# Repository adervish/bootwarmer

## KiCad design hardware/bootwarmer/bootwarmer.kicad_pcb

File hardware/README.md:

# Bootwarmer controller board (rev C, integrated)

One board per boot. Each board carries an ESP32-C6 module, one 18650 cell, a
USB-C port for charging and flashing, one heater output, one thermistor input,
and an IMU. JLCPCB places every part except the through-hole battery holder.

Status: **unbuilt first article.** The design passes KiCad's electrical and
design-rule checks and the netlist is verified against the design file, but no
board has been made or powered. Read "Before you order" below.

## What is on the board

| Block | Parts | Notes |
|---|---|---|
| MCU | U1 (ESP32-C6-MINI-1-N4) | Bluetooth LE; built-in antenna overhangs the end of the cell |
| Battery | MPD BH-18650-PC holder on the back | The only hand-soldered part: two through-hole joints |
| Reverse-polarity protection | Q1, Q2 (AO3401A), R6 | A cell inserted backwards is blocked |
| Cell protection | U3 (DW01A), Q3, Q4 (AO3400A) | Over-discharge, over-charge, short circuit; trips at roughly 2.5-3 A |
| USB-C and charger | J1, U5, U2 (TP4056), about 0.6 A | Red = charging, green = done. Same port flashes firmware |
| 3.3 V supply | U4 (ME6211), SW1 | The slide switch enables the regulator |
| Heater output | J2, Q5 (AO3400A), R23, R24, C3 | Low-side switch, 100 Hz PWM, off by default |
| Thermistor input | J4, R21 (5.1k), C12 | 10k NTC (B3950) between the two pins |
| IMU | U6 (LSM6DS3TR-C), I2C address 0x6A | |
| Status | LED3, SW2 (BOOT) | |
| Test pads | TP1 GND, TP2 3V3, TP3 VSYS | |

Board: 107 x 27.4 mm, 2 layers, about 24 mm thick with the holder.

## Pin map

| GPIO | Net | Use |
|---|---|---|
| IO14 | HTR1 | Heater MOSFET gate, high = heat |
| IO1 | NTC1 | Thermistor divider (ADC) |
| IO0 | VBAT_SENSE | Battery voltage / 2 (ADC) |
| IO6 | VBUS_SENSE | USB present, VBUS / 2 (ADC) |
| IO7 / IO18 | SDA / SCL | IMU |
| IO19 | IMU_INT | IMU interrupt 1 |
| IO8 | LED_STAT | Status LED, low = on (strapping pin, pulled high) |
| IO9 | BOOT | Boot button to ground (strapping pin, pulled high) |
| IO12 / IO13 | USB_DN / USB_DP | USB-C data |

## Ordering from JLCPCB

Files are in `fab/`:

1. Upload `bootwarmer-gerbers.zip`. 2 layers, 1.6 mm, LeadFree HASL.
2. Turn on PCB Assembly, **Standard** type, top side. The ESP32 module and the
   IMU are not available with Economic assembly.
3. Upload `bootwarmer-bom.csv` and `bootwarmer-cpl.csv`. 54 parts are placed.
4. Confirm stock for every line. The module (C5736265) has been out of stock at
   times; the -H4 and -N8 variants of ESP32-C6-MINI-1 use the same footprint.
5. Set Confirm Parts Placement to Yes and check the placement preview.
   JLCPCB's rotation convention differs from KiCad's for some packages. Look at
   U1, U2, U3, U4, U5, U6, the SOT-23 transistors, the LEDs, J1 and SW1.
6. J2 and J4 use a JST-PH-compatible connector (CJT A2001WR-S-2P) on a footprint
   drawn for the genuine JST part. Check that they sit on their pads.

Parts you add yourself:

- **BT1**: MPD BH-18650-PC holder, soldered on the back. `+` end is at the USB end.
- Heater and thermistor leads need JST PH 2-pin plugs.

## Before you order

- **Heater resistance.** The heater runs from 3.0-4.2 V. A pad of about
  2.5-3.5 ohms gives roughly 4-6 W. Pads sized for 5 V will make about half
  their rated heat. Keep heater current under 2 A (connector rating).
- **Run time.** A 3000 mAh cell holds about 11 Wh: roughly 2 hours at a
  continuous 5 W, longer when the PID loop is cycling, less in the cold.
- **Thermal cutoff.** Firmware cuts the heater at 130 F and on any sensor
  fault, and a watchdog resets a hung controller. Nothing independent of
  firmware limits pad temperature. A 60 C thermal fuse in series with the pad,
  taped to it, is strongly recommended.
- **Unprotected flat-top 18650 cells.** Protected cells are usually too long
  for this holder. The spring contacts can bounce under hard impacts.
- **Thermistor accuracy** assumes a 3.3 V rail. Below about 3.4 V of battery
  the rail sags and readings drift; firmware stops heating at 3.3 V.
- The heater current loop is laid out by hand with wide copper; the rest is
  autorouted. Open `bootwarmer/bootwarmer.kicad_pcb` in KiCad and look it over.

## Bring-up

1. Before fitting the holder, check for shorts with a meter: VSYS to GND and
   3V3 to GND.
2. Solder the holder. Insert a cell. TP3 (VSYS) may read 0 V until the charger
   wakes the protection chip; plugging in USB once does that.
3. Switch ON. TP2 should read 3.3 V and the status LED should blink.
4. Plug in USB-C. The red LED lights while charging. Heating is disabled
   whenever USB is plugged in.
5. Flash `src/esp32c6/bootwarmer` (board: ESP32C6 Dev Module, USB CDC On Boot
   enabled). If the port does not appear, hold BOOT while switching ON.
6. Plug in a thermistor and heater, unplug USB, and connect with the app.
   A new board comes up as left; the app's control packet can reassign it.

## Regenerating

Everything is generated from `scripts/design.py`. Edit that file, then run
`./build.sh`. It rebuilds the schematic, places and autoroutes the board,
pours and stitches the ground planes, runs ERC and DRC, verifies both netlists
against the design file, and rewrites `fab/`.

Requirements: KiCad 10, Freerouting 2.5 jar at
`~/.local/share/freerouting/freerouting.jar`, and Java 25 or newer
(`brew install openjdk`).

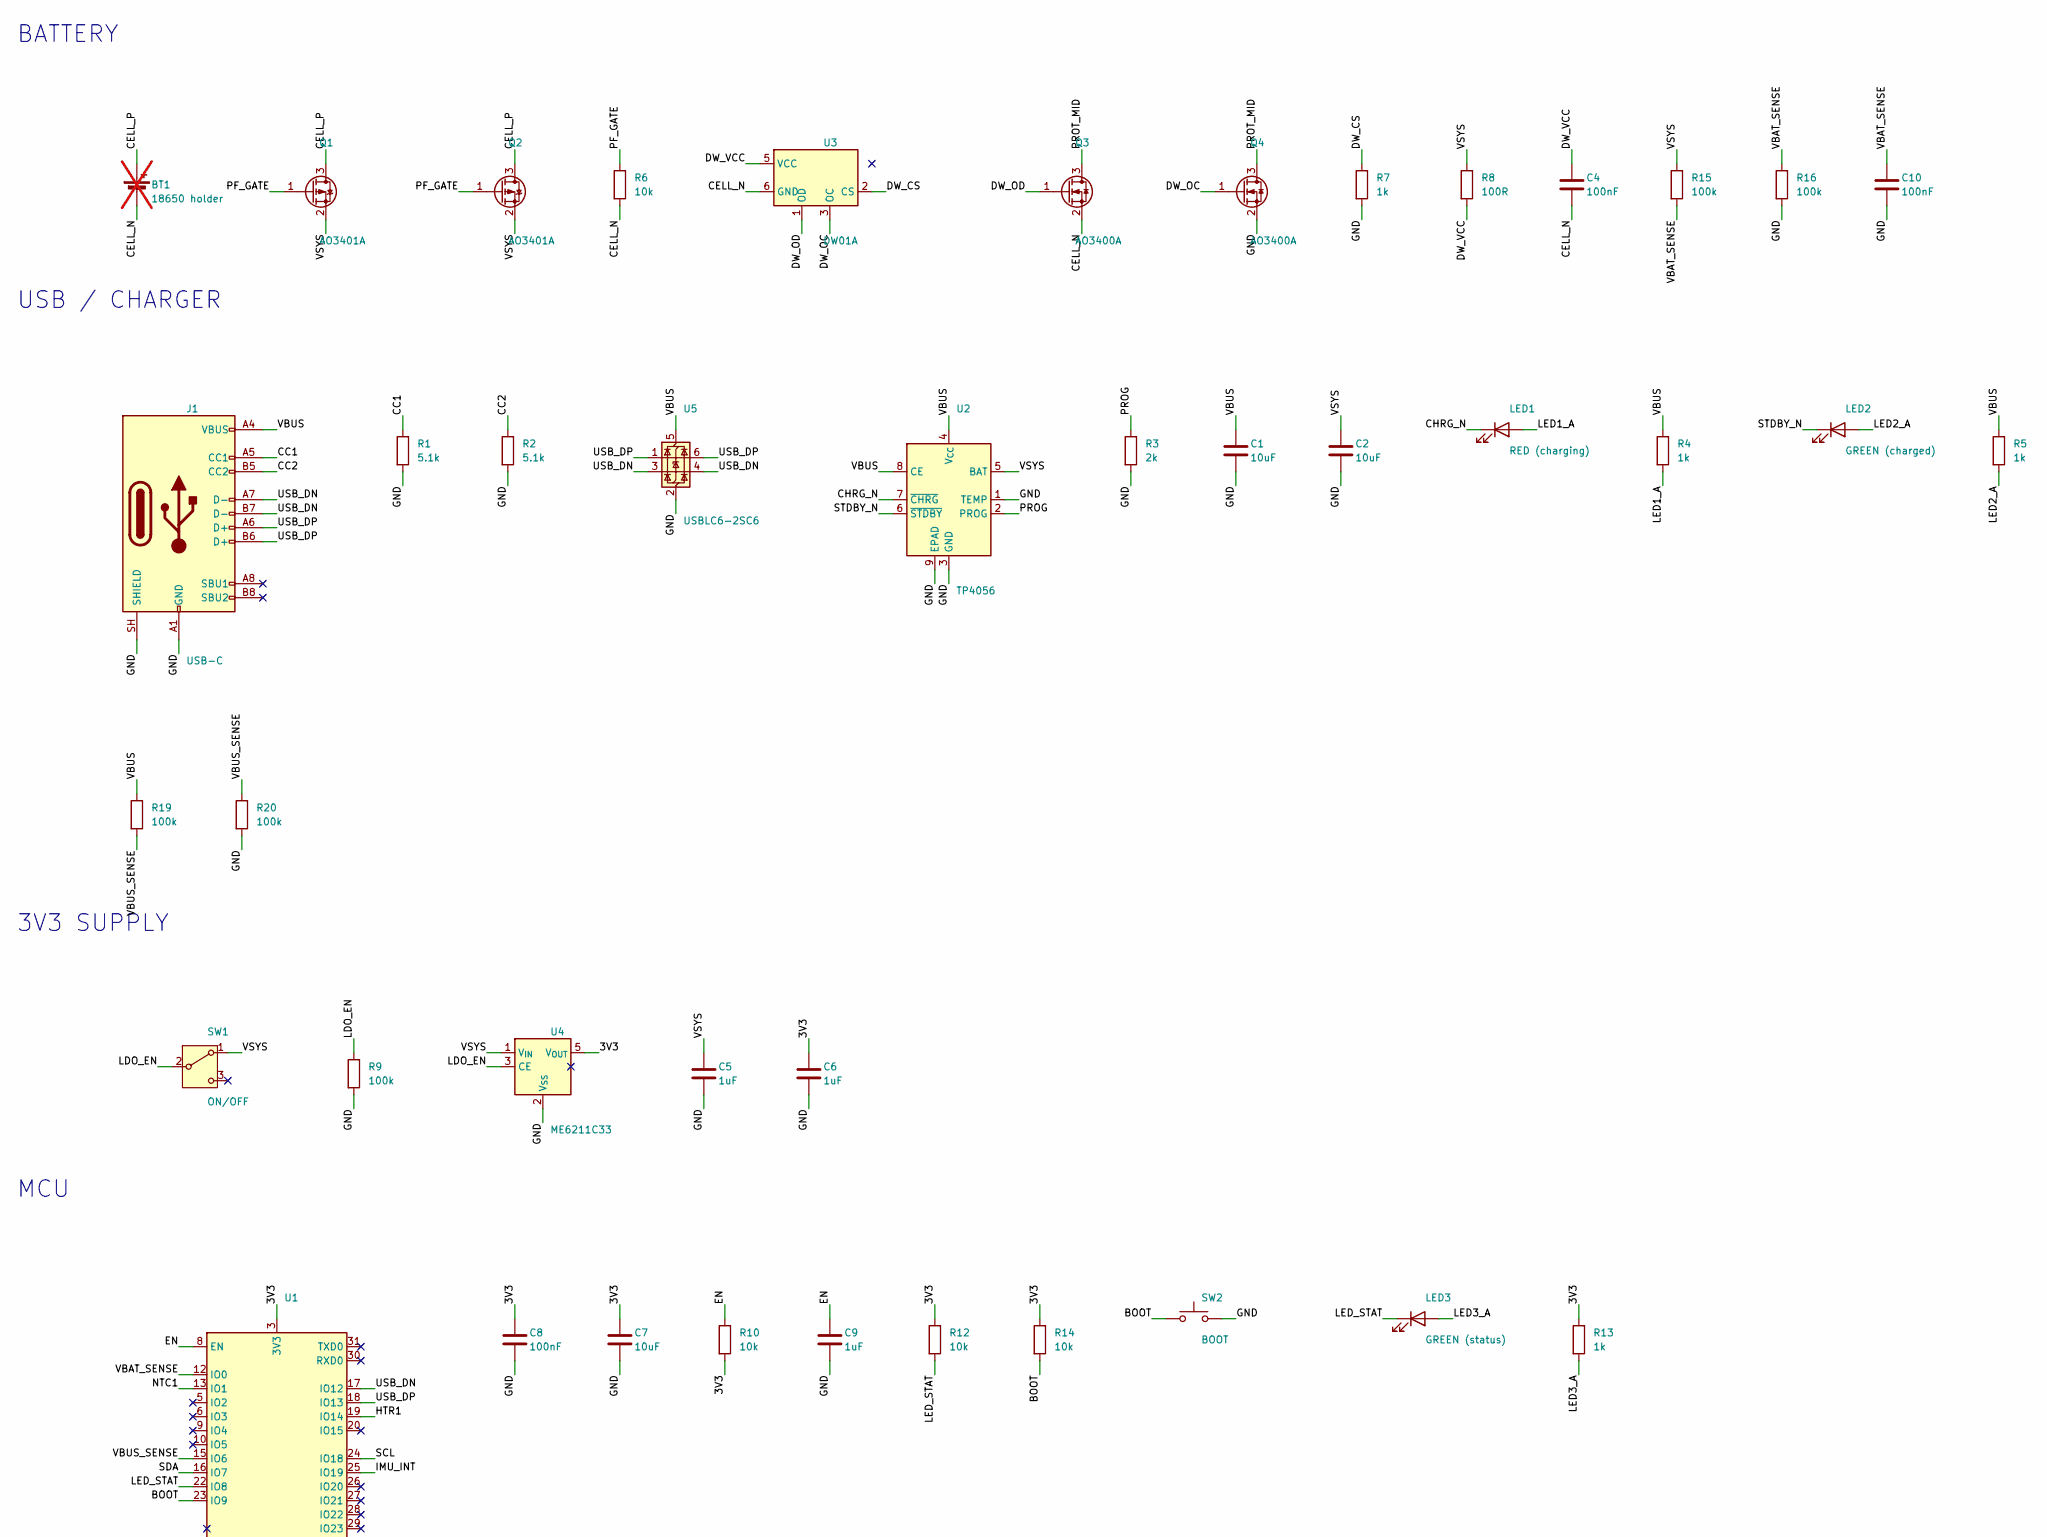
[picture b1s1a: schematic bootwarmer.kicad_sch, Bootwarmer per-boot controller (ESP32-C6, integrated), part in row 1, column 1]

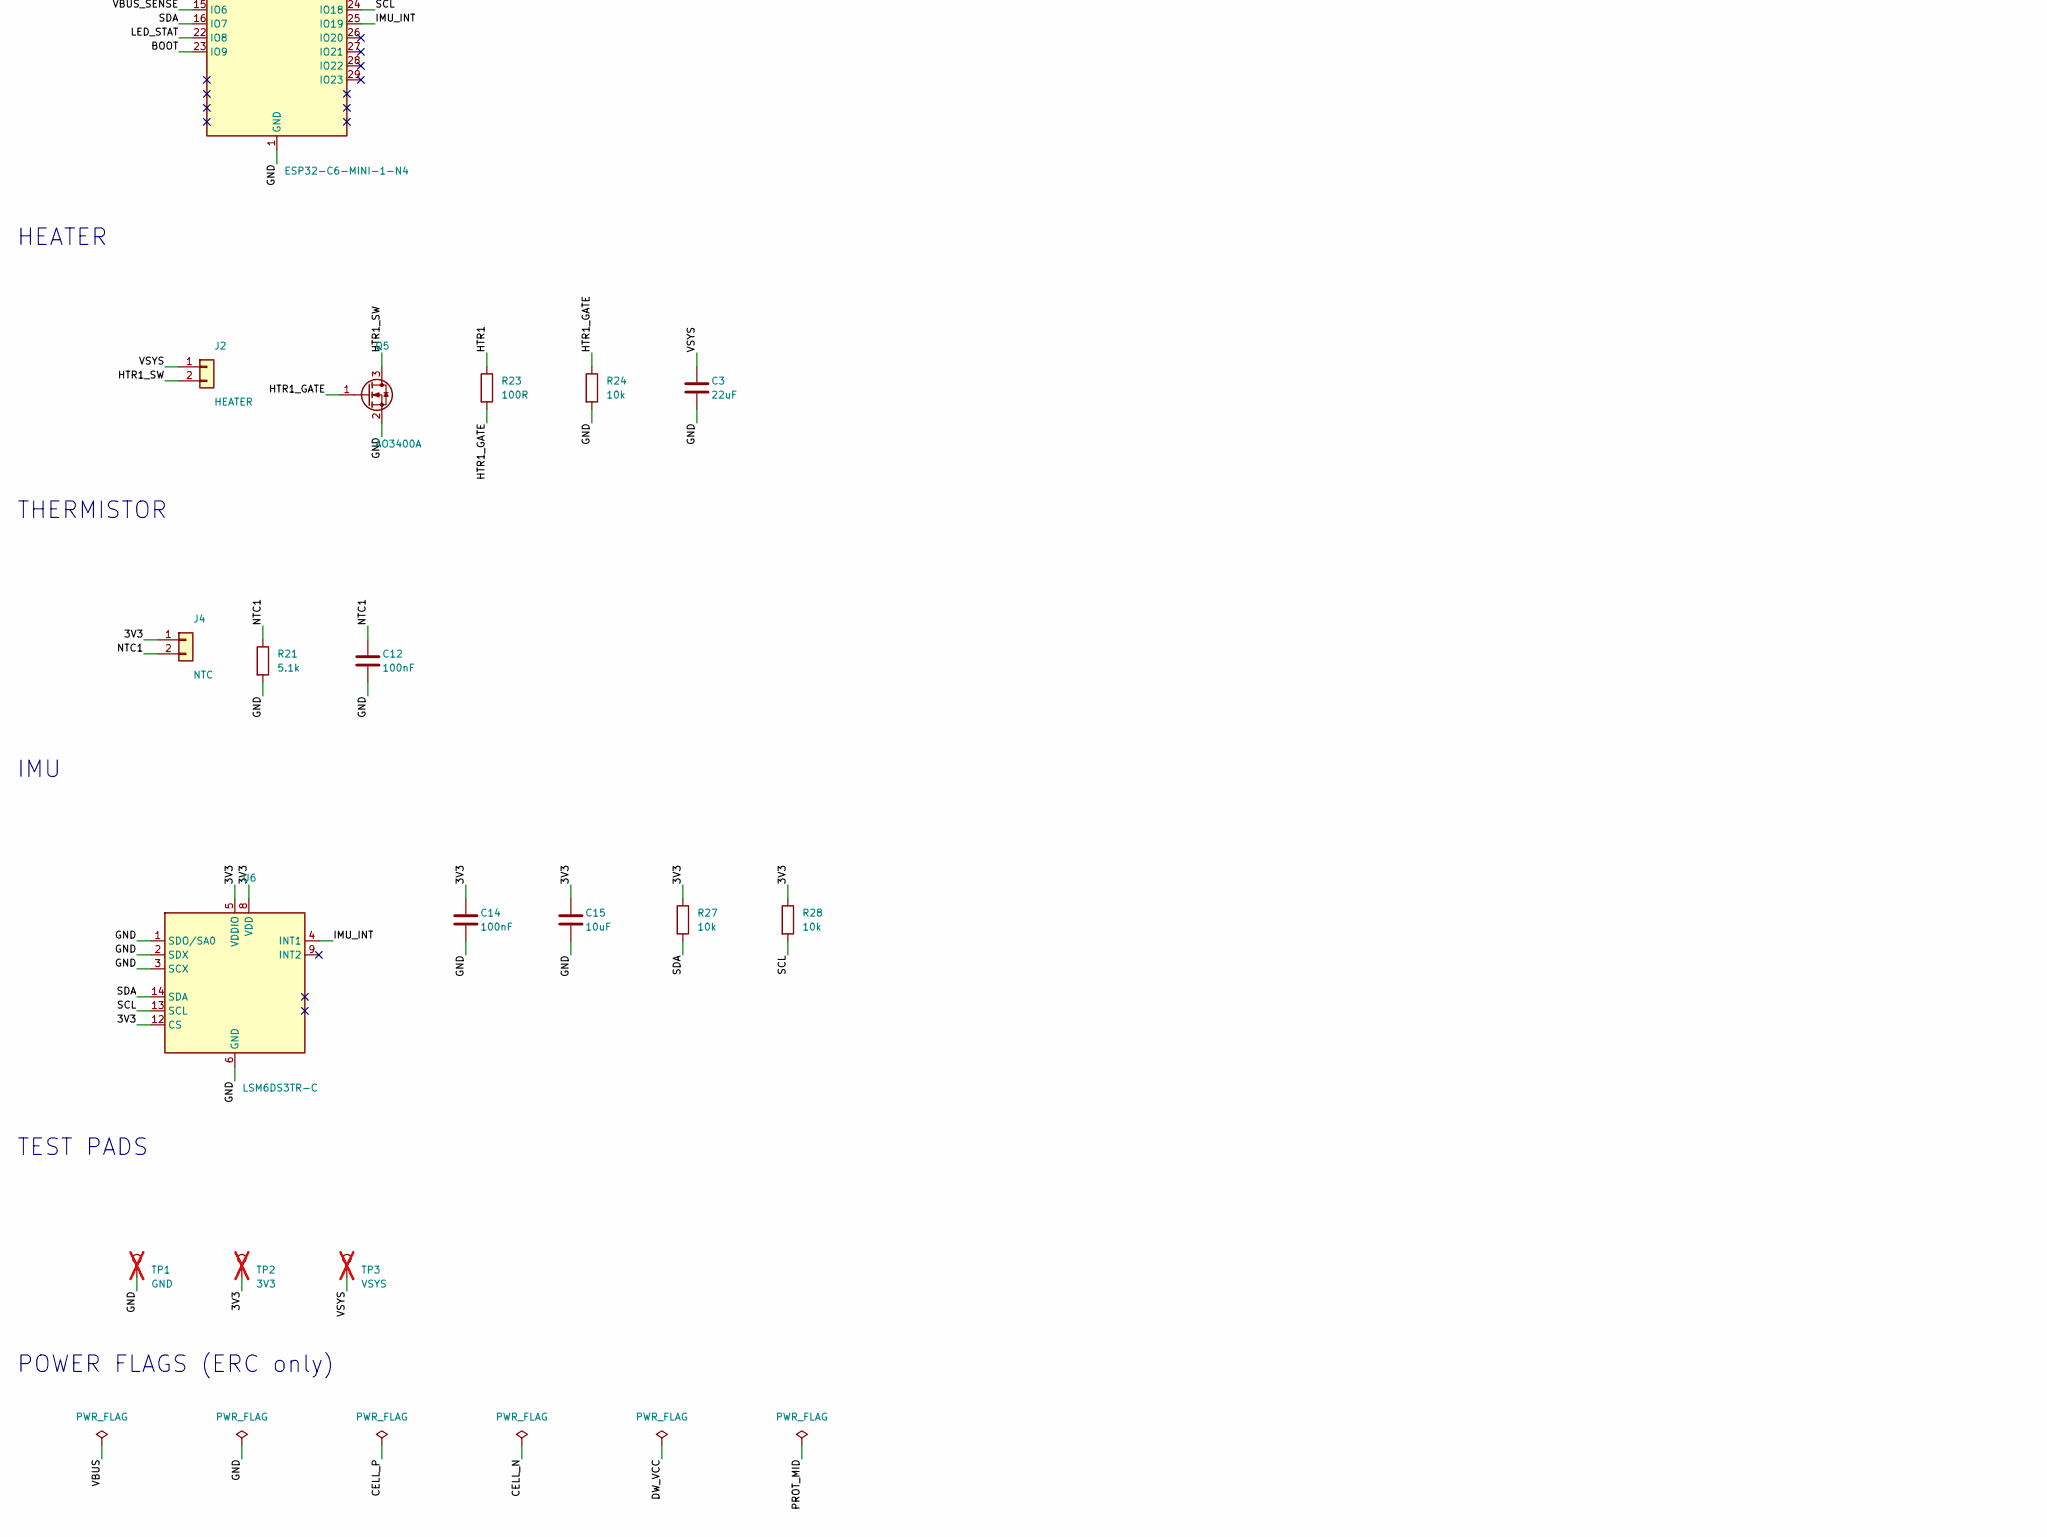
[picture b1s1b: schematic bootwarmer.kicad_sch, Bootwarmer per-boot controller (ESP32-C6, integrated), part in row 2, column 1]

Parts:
BT1: 18650 holder; BatteryHolder_MPD_BH-18650-PC; MPN MPD BH-18650-PC (hand solder); not fitted
C1, C2, C7, C15: 10uF; C_0603_1608Metric; MPN 10uF; LCSC C19702
C3: 22uF; C_0805_2012Metric; MPN 22uF; LCSC C45783
C4, C8, C10, C12, C14: 100nF; C_0603_1608Metric; MPN 100nF; LCSC C14663
C5, C6, C9: 1uF; C_0603_1608Metric; MPN 1uF; LCSC C15849
J1: USB-C; USB_C_Receptacle_HRO_TYPE-C-31-M-12; MPN HRO TYPE-C-31-M-12; LCSC C165948
J2: HEATER; JST_PH_S2B-PH-SM4-TB_1x02-1MP_P2.00mm_Horizontal; MPN CJT A2001WR-S-2P (JST PH compatible); LCSC C225233
J4: NTC; JST_PH_S2B-PH-SM4-TB_1x02-1MP_P2.00mm_Horizontal; MPN CJT A2001WR-S-2P (JST PH compatible); LCSC C225233
LED1: RED (charging); LED_0603_1608Metric; MPN KT-0603R; LCSC C2286
LED2: GREEN (charged); LED_0603_1608Metric; MPN XL-1608UGC-04; LCSC C965804
LED3: GREEN (status); LED_0603_1608Metric; MPN XL-1608UGC-04; LCSC C965804
Q1, Q2: AO3401A; SOT-23; MPN AO3401A; LCSC C15127
Q3, Q4, Q5: AO3400A; SOT-23; MPN AO3400A; LCSC C20917
R1, R2, R21: 5.1k; R_0603_1608Metric; MPN 5.1k; LCSC C23186
R3: 2k; R_0603_1608Metric; MPN 2k; LCSC C22975
R4, R5, R7, R13: 1k; R_0603_1608Metric; MPN 1k; LCSC C21190
R6, R10, R12, R14, R24, R27, R28: 10k; R_0603_1608Metric; MPN 10k; LCSC C25804
R8, R23: 100R; R_0603_1608Metric; MPN 100R; LCSC C22775
R9, R15, R16, R19, R20: 100k; R_0603_1608Metric; MPN 100k; LCSC C25803
SW1: ON/OFF; SW_SPDT_Shouhan_MSK12C02; MPN MSK12C02; LCSC C431540
SW2: BOOT; SW_Push_1P1T_XKB_TS-1187A; MPN TS-1187A-B-A-B; LCSC C318884
TP1: GND; TestPoint_Pad_D1.5mm; MPN GND; not fitted
TP2: 3V3; TestPoint_Pad_D1.5mm; MPN 3V3; not fitted
TP3: VSYS; TestPoint_Pad_D1.5mm; MPN VSYS; not fitted
U1: ESP32-C6-MINI-1-N4; ESP32-C6-MINI-1; MPN ESP32-C6-MINI-1-N4; LCSC C5736265
U2: TP4056; SOIC-8-1EP_3.9x4.9mm_P1.27mm_EP2.41x3.3mm; MPN TP4056-42-ESOP8; LCSC C16581
U3: DW01A; SOT-23-6; MPN DW01A; LCSC C351410
U4: ME6211C33; SOT-23-5; MPN ME6211C33M5G-N; LCSC C82942
U5: USBLC6-2SC6; SOT-23-6; MPN USBLC6-2SC6; LCSC C7519
U6: LSM6DS3TR-C; LGA-14_3x2.5mm_P0.5mm_LayoutBorder3x4y; MPN LSM6DS3TR-C; LCSC C967633

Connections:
3V3: C6.1, C7.1, C8.1, C14.1, C15.1, J4.1, R10.2, R12.1, R13.1, R14.1, R27.1, R28.1, TP2.1, U1.3 (3V3), U4.5 (V_{OUT}), U6.5 (VDDIO), U6.8 (VDD), U6.12 (CS)
BOOT: R14.2, SW2.1, U1.23 (IO9)
CC1: J1.A5 (CC1), R1.1
CC2: J1.B5 (CC2), R2.1
CELL_N: BT1.2 (-), C4.2, Q3.2 (S), R6.2, U3.6 (GND)
CELL_P: BT1.1 (+), Q1.3 (D), Q2.3 (D)
CHRG_N: LED1.1 (K), U2.7 (~CHRG)
DW_CS: R7.1, U3.2 (CS)
DW_OC: Q4.1 (G), U3.3 (OC)
DW_OD: Q3.1 (G), U3.1 (OD)
DW_VCC: C4.1, R8.2, U3.5 (VCC)
EN: C9.1, R10.1, U1.8 (EN)
GND: C1.2, C2.2, C3.2, C5.2, C6.2, C7.2, C8.2, C9.2, C10.2, C12.2, C14.2, C15.2, J1.A1 (GND), J1.A12 (GND), J1.B1 (GND), J1.B12 (GND), J1.SH (SHIELD), J2.MP, J4.MP, Q4.2 (S), Q5.2 (S), R1.2, R2.2, R3.2, R7.2, R9.2, R16.2, R20.2, R21.2, R24.2, SW1.SH, SW2.2, TP1.1, U1.1 (GND), U1.2 (GND), U1.11 (GND), U1.14 (GND), U1.36 (GND), U1.37 (GND), U1.38 (GND), U1.39 (GND), U1.40 (GND), U1.41 (GND), U1.42 (GND), U1.43 (GND), U1.44 (GND), U1.45 (GND), U1.46 (GND), U1.47 (GND), U1.48 (GND), U1.49 (GND), U1.50 (GND), U1.51 (GND), U1.52 (GND), U1.53 (GND), U2.1 (TEMP), U2.3 (GND), U2.9 (EPAD), U4.2 (V_{SS}), U5.2 (GND), U6.1 (SDO/SA0), U6.2 (SDX), U6.3 (SCX), U6.6 (GND), U6.7 (GND)
HTR1: R23.1, U1.19 (IO14)
HTR1_GATE: Q5.1 (G), R23.2, R24.1
HTR1_SW: J2.2, Q5.3 (D)
IMU_INT: U1.25 (IO19), U6.4 (INT1)
LDO_EN: R9.1, SW1.2 (B), U4.3 (CE)
LED1_A: LED1.2 (A), R4.2
LED2_A: LED2.2 (A), R5.2
LED3_A: LED3.2 (A), R13.2
LED_STAT: LED3.1 (K), R12.2, U1.22 (IO8)
NTC1: C12.1, J4.2, R21.1, U1.13 (IO1)
PF_GATE: Q1.1 (G), Q2.1 (G), R6.1
PROG: R3.1, U2.2 (PROG)
PROT_MID: Q3.3 (D), Q4.3 (D)
SCL: R28.2, U1.24 (IO18), U6.13 (SCL)
SDA: R27.2, U1.16 (IO7), U6.14 (SDA)
STDBY_N: LED2.1 (K), U2.6 (~STDBY)
USB_DN: J1.A7 (D-), J1.B7 (D-), U1.17 (IO12), U5.3 (I/O2), U5.4 (I/O2)
USB_DP: J1.A6 (D+), J1.B6 (D+), U1.18 (IO13), U5.1 (I/O1), U5.6 (I/O1)
VBAT_SENSE: C10.1, R15.2, R16.1, U1.12 (IO0)
VBUS: C1.1, J1.A4 (VBUS), J1.A9 (VBUS), J1.B4 (VBUS), J1.B9 (VBUS), R4.1, R5.1, R19.1, U2.4 (V_{CC}), U2.8 (CE), U5.5 (VBUS)
VBUS_SENSE: R19.2, R20.1, U1.15 (IO6)
VSYS: C2.1, C3.1, C5.1, J2.1, Q1.2 (S), Q2.2 (S), R8.1, R15.1, SW1.1 (A), TP3.1, U2.5 (BAT), U4.1 (V_{IN})

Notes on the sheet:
BATTERY
USB / CHARGER
3V3 SUPPLY
MCU
HEATER
THERMISTOR
IMU
TEST PADS
POWER FLAGS (ERC only)

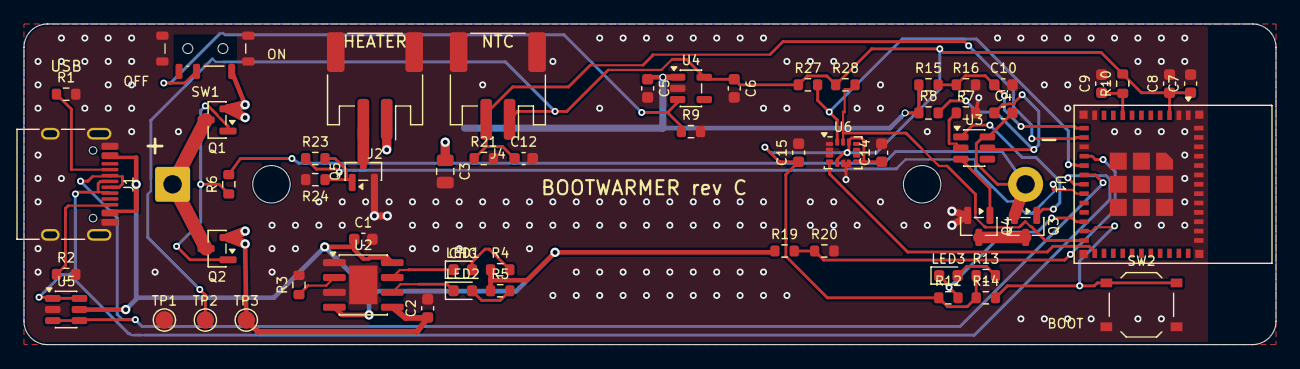
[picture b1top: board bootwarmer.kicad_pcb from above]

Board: 2 copper layers, 107.0 x 27.4 mm, 58 parts (1 on the bottom side), 35 nets.

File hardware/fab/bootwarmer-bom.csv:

Comment,Designator,Footprint,LCSC Part #
AO3401A,"Q1,Q2",SOT-23,C15127
10k,"R6,R10,R12,R14,R24,R27,R28",R_0603_1608Metric,C25804
DW01A,U3,SOT-23-6,C351410
AO3400A,"Q3,Q4,Q5",SOT-23,C20917
1k,"R7,R4,R5,R13",R_0603_1608Metric,C21190
100R,"R8,R23",R_0603_1608Metric,C22775
100nF,"C4,C10,C8,C12,C14",C_0603_1608Metric,C14663
100k,"R15,R16,R19,R20,R9",R_0603_1608Metric,C25803
HRO TYPE-C-31-M-12,J1,USB_C_Receptacle_HRO_TYPE-C-31-M-12,C165948
5.1k,"R1,R2,R21",R_0603_1608Metric,C23186
USBLC6-2SC6,U5,SOT-23-6,C7519
TP4056-42-ESOP8,U2,SOIC-8-1EP_3.9x4.9mm_P1.27mm_EP2.41x3.3mm,C16581
2k,R3,R_0603_1608Metric,C22975
10uF,"C1,C2,C7,C15",C_0603_1608Metric,C19702
KT-0603R,LED1,LED_0603_1608Metric,C2286
XL-1608UGC-04,"LED2,LED3",LED_0603_1608Metric,C965804
MSK12C02,SW1,SW_SPDT_Shouhan_MSK12C02,C431540
ME6211C33M5G-N,U4,SOT-23-5,C82942
1uF,"C5,C6,C9",C_0603_1608Metric,C15849
ESP32-C6-MINI-1-N4,U1,ESP32-C6-MINI-1,C5736265
TS-1187A-B-A-B,SW2,SW_Push_1P1T_XKB_TS-1187A,C318884
CJT A2001WR-S-2P (JST PH compatible),"J2,J4",JST_PH_S2B-PH-SM4-TB_1x02-1MP_P2.00mm_Horizontal,C225233
22uF,C3,C_0805_2012Metric,C45783
LSM6DS3TR-C,U6,LGA-14_3x2.5mm_P0.5mm_LayoutBorder3x4y,C967633

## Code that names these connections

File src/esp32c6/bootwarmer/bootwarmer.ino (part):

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
const int PIN_HEATER = 14;
const int PIN_NTC = 1;
const int PIN_VBAT_SENSE = 0;
const int PIN_VBUS_SENSE = 6;
const int PIN_SDA = 7;
const int PIN_SCL = 18;
const int PIN_IMU_INT = 19;
const int PIN_LED = 8;            // active low

const int PWM_FREQ = 100;
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// rough straight-line estimate between empty (3.3 V) and full (4.2 V).
void batteryRead(float &volts, float &percent) {
  uint32_t mv = 0;
  for (int i = 0; i < 8; i++) mv += analogReadMilliVolts(PIN_VBAT_SENSE);
  volts = (mv / 8) * 2 / 1000.0;
  percent = constrain((volts - 3.3f) / (4.2f - 3.3f) * 100.0f, 0.0f, 100.0f);
}
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}

bool usbPresent() {
  return analogReadMilliVolts(PIN_VBUS_SENSE) * 2 > 4000;
}

void setHeater(uint8_t percent) {
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
  analogReadResolution(12);
  analogSetAttenuation(ADC_11db);
  pinMode(PIN_IMU_INT, INPUT);

  pinMode(PIN_LED, OUTPUT);
  digitalWrite(PIN_LED, HIGH);
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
